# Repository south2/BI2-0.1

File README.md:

# BI2-0.1
body interaction 2 vibrator development board (version 0.1)

www.bodyinteraction.org

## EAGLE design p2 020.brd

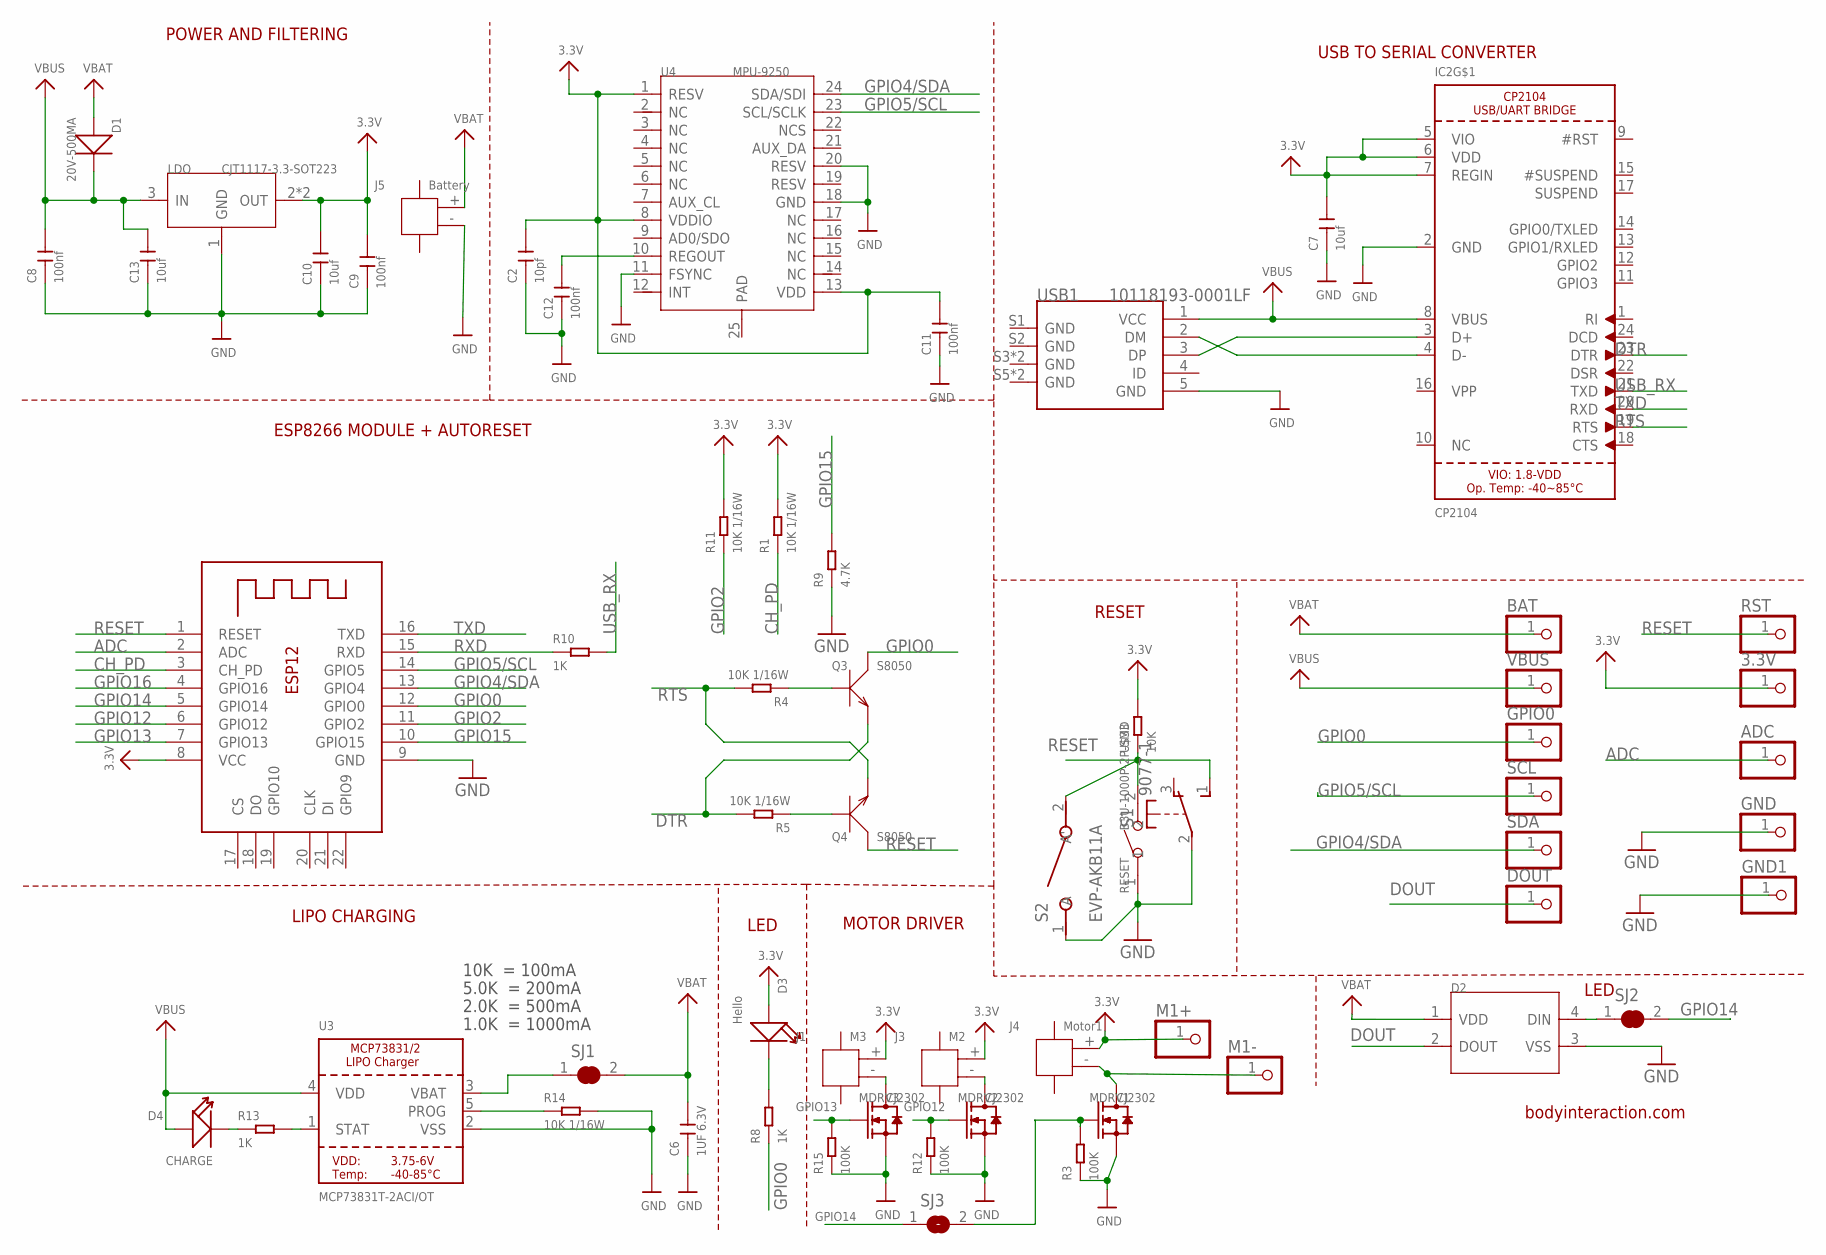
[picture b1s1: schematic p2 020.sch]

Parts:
3.3V: PINHD-1X1; 1X01
ADC: PINHD-1X1; 1X01
BAT: PINHD-1X1; 1X01
C2: 10pf; C0402
C6: 1UF 6.3V; C0402
C7, C10, C13: 10uf; C0402
C8, C9, C11, C12: 100nf; C0402
D1: 20V-500MA; SOD-123
D2: SMD-RGB-LED-4P'WS2812B'; LED4-SMD-5050
D3: Hello; LED-0603
D4: CHARGE; LED-0402
DOUT: PINHD-1X1; 1X01
ESP: ESP-12; ESP-12E
GND, GND1: PINHD-1X1; 1X01
GPIO0: PINHD-1X1; 1X01
IC2: CP2104; QFN24_4MM_SMSC
J1: M3; HW2-SMD-1.0-90D
J3: M2; HW2-SMD-1.0-90D
J4: Motor1; HW2-SMD-1.0-90D
J5: Battery; HW2-SMD-1.0-90D
LDO: CJT1117-3.3-SOT223; SOT-223
M1+, M1-: PINHD-1X1; 1X01
MDRV1, MDRV2, MDRV3: CJ2302; SOT-23
Q3, Q4: S8050; SOT-23
R1, R4, R5, R11, R14: 10K 1/16W; R0402
R3, R12, R15: 100K; R0402
R8, R10, R13: 1K; R0402
R9: 4.7K; R0402
RESET: B3U-1000P-2P-SMD; SW2-2.6-3.0X2.5X1.2+0.4MM
RST: PINHD-1X1; 1X01
S1: 9077-1
S2: EVP-AKB11A; SW_EVP-AKB11A
SCL: PINHD-1X1; 1X01
SDA: PINHD-1X1; 1X01
SJ1, SJ2: SOLDERJUMPER_CLOSED; SOLDERJUMPER_CLOSEDWIRE
SJ3: SJ
U3: MCP73831T-2ACI/OT; SOT23-5
U4: MPU-9250; QFN24G-0.4-3X3MM
U$33: 10K; R0402
USB1: 10118193-0001LF; MICRO-USB5+6P-SMD-0.65-B
VBUS: PINHD-1X1; 1X01

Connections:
3.3V: 3.3V.1, C2.2, C7.2, C9.2, C10.2, C11.2, D3.+, ESP.8 (VCC), IC2.5 (VIO), IC2.6 (VDD), IC2.7 (REGIN), J1.+ (1), J3.+ (1), J4.+ (1), LDO.2 (OUT), LDO.TER (OUT), M1+.1, R1.2, R11.2, U4.1 (RESV), U4.8 (VDDIO), U4.13 (VDD), U$33.2
ADC: ADC.1, ESP.2 (ADC)
CH_PD: ESP.3 (CH_PD), R1.1
DOUT: D2.2 (DOUT), DOUT.1
DTR: IC2.23 (DTR), Q3.2 (E), R5.2
GND: C2.1, C6.1, C7.1, C8.1, C9.1, C10.1, C11.1, C12.1, C13.1, D2.3 (VSS), ESP.9 (GND), GND.1, GND1.1, IC2.2 (GND), J5.- (2), LDO.1 (GND), MDRV1.2 (S), MDRV2.2 (S), MDRV3.2 (S), R3.1, R9.1, R12.1, R14.2, R15.1, RESET.1, S1.2, S2.1 (A), U3.2 (VSS), U4.11 (FSYNC), U4.18 (GND), U4.20 (RESV), USB1.5 (GND)
GPIO0: ESP.12 (GPIO0), GPIO0.1, Q3.3 (C), R8.1
GPIO2: ESP.11 (GPIO2), R11.1
GPIO4/SDA: ESP.13 (GPIO4), SDA.1, U4.24 (SDA/SDI)
GPIO5/SCL: ESP.14 (GPIO5), SCL.1, U4.23 (SCL/SCLK)
GPIO12: ESP.6 (GPIO12), MDRV2.1 (G), R12.2
GPIO13: ESP.7 (GPIO13), MDRV3.1 (G), R15.2
GPIO14: ESP.5 (GPIO14), SJ2.2, SJ3.1
GPIO15: ESP.10 (GPIO15), R9.2
GPIO16: ESP.4 (GPIO16)
unnamed: J3.- (2), MDRV2.3 (D)
unnamed: D4.-, R13.1
unnamed: J4.- (2), M1-.1, MDRV1.3 (D)
unnamed: IC2.3 (D+), USB1.3 (DP)
unnamed: D3.-, R8.2
unnamed: D2.4 (DIN), SJ2.1
unnamed: IC2.4 (D-), USB1.2 (DM)
unnamed: MDRV1.1 (G), R3.2, SJ3.2
unnamed: C12.2, U4.10 (REGOUT)
unnamed: Q4.1 (B), R5.1
unnamed: Q3.1 (B), R4.1
unnamed: R13.2, U3.1 (STAT)
unnamed: R14.1, U3.5 (PROG)
unnamed: SJ1.1, U3.3 (VBAT)
unnamed: J1.- (2), MDRV3.3 (D)
RESET: ESP.1 (RESET), Q4.3 (C), RESET.2, RST.1, S1.1 (S), S2.2 (A'), U$33.1
RTS: IC2.19 (RTS), Q4.2 (E), R4.2
RXD: ESP.15 (RXD), R10.1
TP: IC2.THERM (TP)
TXD: ESP.16 (TXD), IC2.20 (RXD)
USB_RX: IC2.21 (TXD), R10.2
VBAT: BAT.1, C6.2, D1.+, D2.1 (VDD), J5.+ (1), SJ1.2
VBUS: C8.2, C13.2, D1.-, D4.+, IC2.8 (VBUS), LDO.3 (IN), U3.4 (VDD), USB1.1 (VCC), VBUS.1

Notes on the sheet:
POWER AND FILTERING
RESET
USB TO SERIAL CONVERTER
LIPO CHARGING
LED
ESP8266 MODULE + AUTORESET
bodyinteraction.com
10K = 100mA
5.0K = 200mA
2.0K = 500mA
1.0K = 1000mA
MOTOR DRIVER

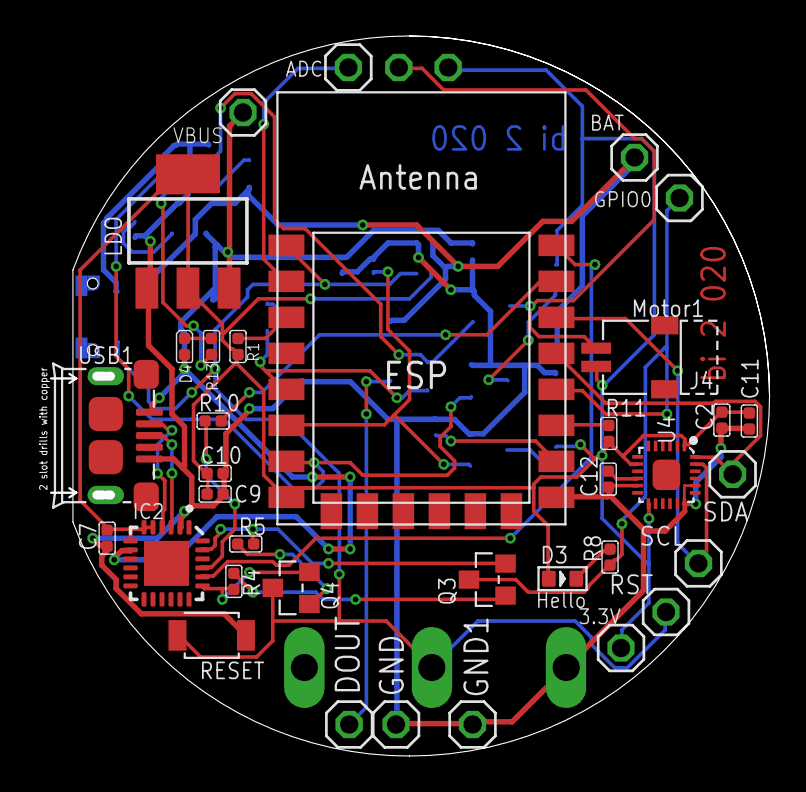
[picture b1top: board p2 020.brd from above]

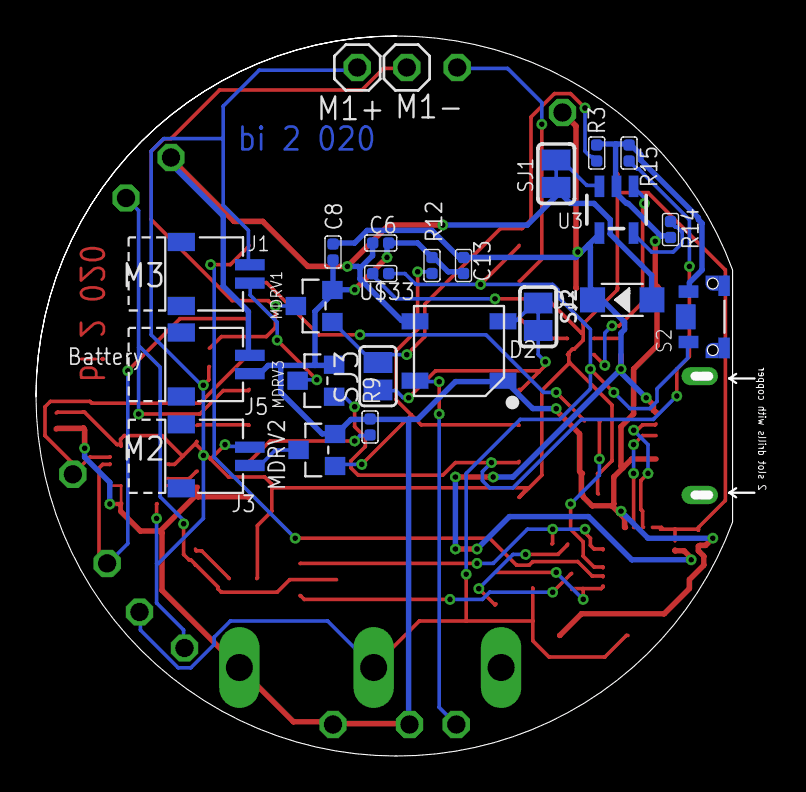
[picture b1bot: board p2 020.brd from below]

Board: 2 copper layers, 40.2 x 39.5 mm, 60 parts (24 on the bottom side), 36 nets.

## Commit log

2018-12-07 Arduino example code for motor and LED control

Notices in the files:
parts and their libraries:
microbuilder: This work is placed in the public domain, and may be freely used for commercial and non-commercial work with the following conditions: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
